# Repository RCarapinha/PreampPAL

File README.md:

# PreampPAL

Project done in 3th year of Masters.

# Description

The goal of this team is to perform a low-noise pre-amplifier that amplifies the needle signal to a line level signal. To accomplish this we started by understanding what was a preamplifier for a record player, namely, what was a preamplifier with reverse RIAA equalization that would amplify the needle signal to a line level signal.

So this team is responsible for the electronics of the turntable audio. This task consists of manipulating low-value and very sensitive voltages. 

# 1st Step: Tests and Simulation

Having said this, we started the search for a preamplifier that corresponded to our needs, i.e. a preamplifier that applied what was described above and low noise (because the values received by the needle are very low).

We chose a range of preamplifiers and set out for the simulation phase using the LTSpice program.

We performed several simulations in LTSpice in terms of noise and equalization in order to choose the best pre-amplifier. At the end of this phase we started to develop the circuit.

# 2nd Step: Breadboard Tests

The first test to be performed was to make sure that the voltage regulator (low noise) correctly converted the value from 5V to 3.3V, and this test was successful. The second test was to verify the amplification and RIAA equalization. For this, a weak signal was applied to the input and we compared the output values obtained with the theoretical output values.

# 3rd Step: PCB Design

After we carried out the tests and validated the operation of the circuit, the next step of the team was to develop the PCB (in EAGLE software) so that we could finish the work.

# 4rd Step: Final Work

Once the PCB has been designed, we start to build the board and assemble the components on it, something that must be done with great care to avoid errors or noise. Finally, we tried to isolate the whole board, for a better functioning.

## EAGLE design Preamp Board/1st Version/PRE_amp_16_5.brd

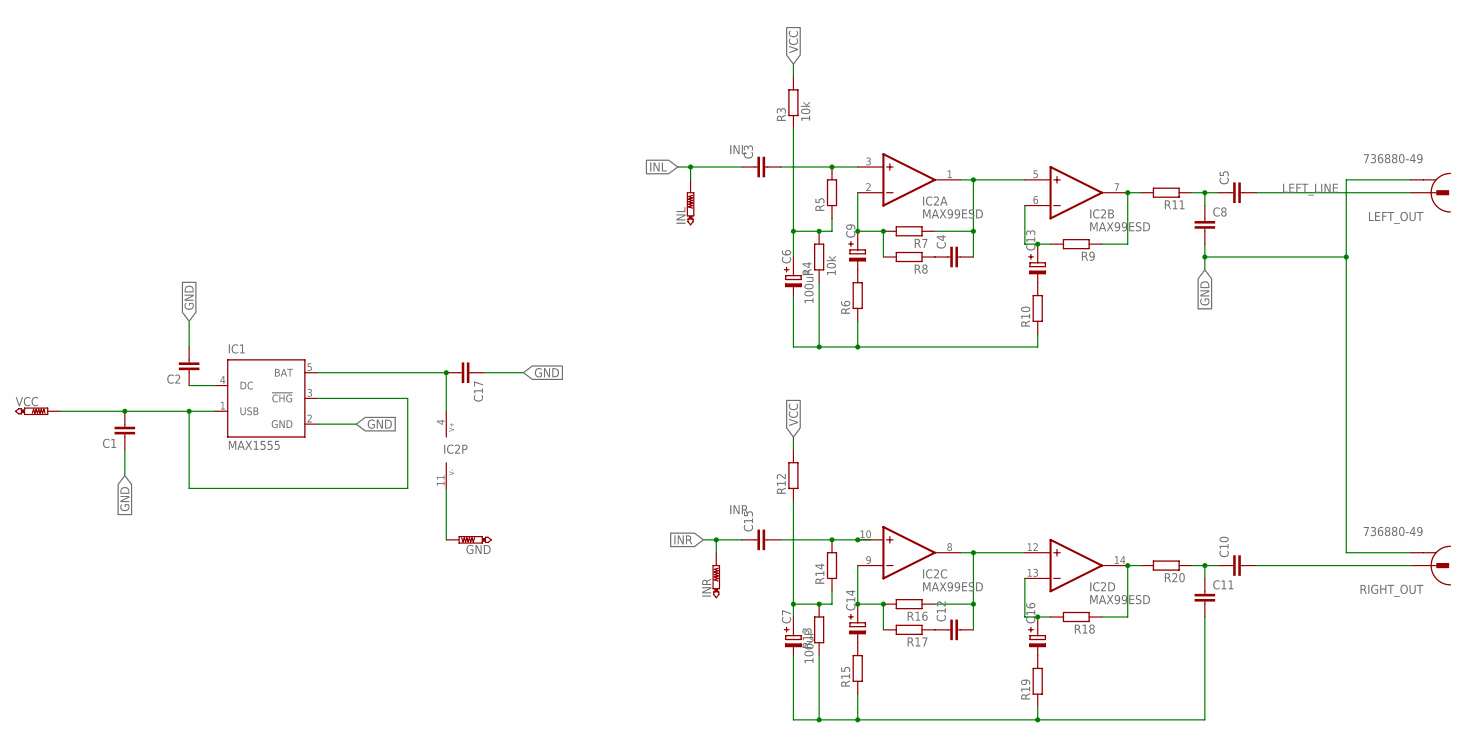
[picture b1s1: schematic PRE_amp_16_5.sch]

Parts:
C1, C2, C3, C4, C5, C8, C10, C11, C12, C15, C17: C-EUC0805; C0805
C6, C7: 100uF; SV-D
C9, C13, C14, C16: C-PR-SMD-SV-B; SV-B
GND: PTR1PAD1-13Y; P1-13Y
IC1: MAX1555; SOT23-5L
IC2: MAX99ESD; SO14
INL: PTR1PAD1-13Y; P1-13Y
INR: PTR1PAD1-13Y; P1-13Y
LEFT_OUT: 736880-49
R3, R4: 10k; R1206
R5, R6, R7, R8, R9, R10, R11, R12, R13, R14, R15, R16, R17, R18, R19, R20: R-EU_R1206; R1206
RIGHT_OUT: 736880-49
VCC: PTR1PAD1-13Y; P1-13Y

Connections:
GND: C1.1, C2.2, C6.-, C7.-, C8.2, C11.2, C17.1, GND.1, IC1.2 (GND), IC2.11 (V-), LEFT_OUT.2, R4.1, R6.1, R10.1, R13.1, R15.1, R19.1, RIGHT_OUT.2
INL: C3.1, INL.1
INR: C15.1, INR.1
LEFT_LINE: C5.2, LEFT_OUT.1
unnamed: C3.2, IC2.3 (+IN), R5.2
unnamed: C6.+, R3.1, R4.2, R5.1
unnamed: C15.2, IC2.10 (+IN), R14.2
unnamed: C7.+, R12.1, R13.2, R14.1
unnamed: IC2.7 (OUT), R9.1, R11.2
unnamed: C9.-, R6.2
unnamed: C4.1, R8.1
unnamed: C12.1, R17.1
unnamed: C9.+, IC2.2 (-IN), R7.2, R8.2
unnamed: C13.-, R10.2
unnamed: C5.1, C8.1, R11.1
unnamed: C14.-, R15.2
unnamed: C13.+, IC2.6 (-IN), R9.2
unnamed: C1.2, IC1.1 (USB), IC1.3 (!CHG), VCC.1
unnamed: C12.2, IC2.8 (OUT), IC2.12 (+IN), R16.1
unnamed: C14.+, IC2.9 (-IN), R16.2, R17.2
unnamed: C16.-, R19.2
unnamed: IC2.14 (OUT), R18.1, R20.2
unnamed: C4.2, IC2.1 (OUT), IC2.5 (+IN), R7.1
unnamed: C16.+, IC2.13 (-IN), R18.2
unnamed: C17.2, IC1.5 (BAT), IC2.4 (V+)
unnamed: C2.1, IC1.4 (DC)
unnamed: C10.2, RIGHT_OUT.1
NS2: C10.1, C11.1, R20.1
VCC: R3.2, R12.2

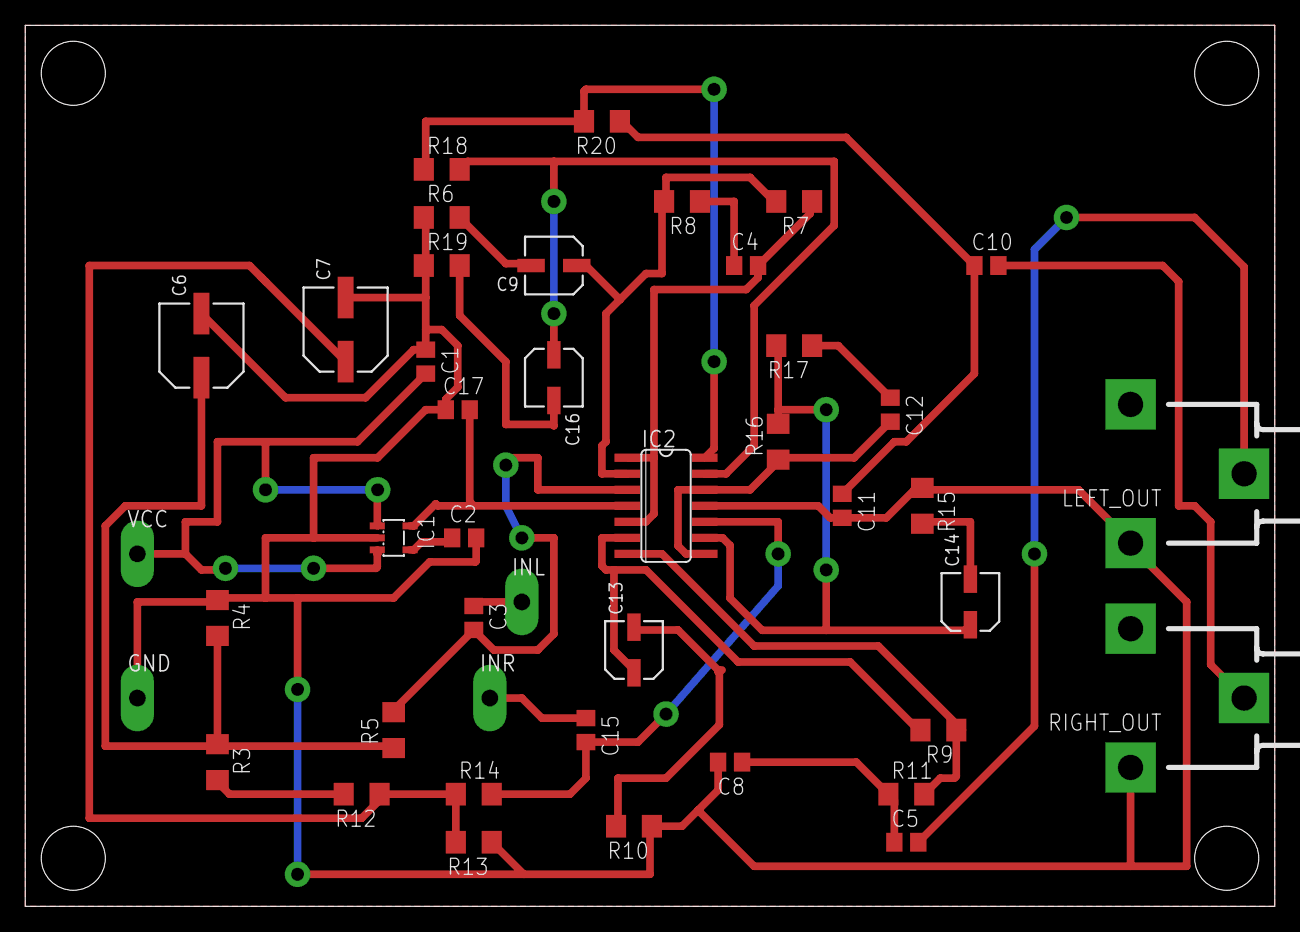
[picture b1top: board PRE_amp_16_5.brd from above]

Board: 2 copper layers, 99.1 x 69.9 mm, 43 parts (0 on the bottom side), 29 nets.

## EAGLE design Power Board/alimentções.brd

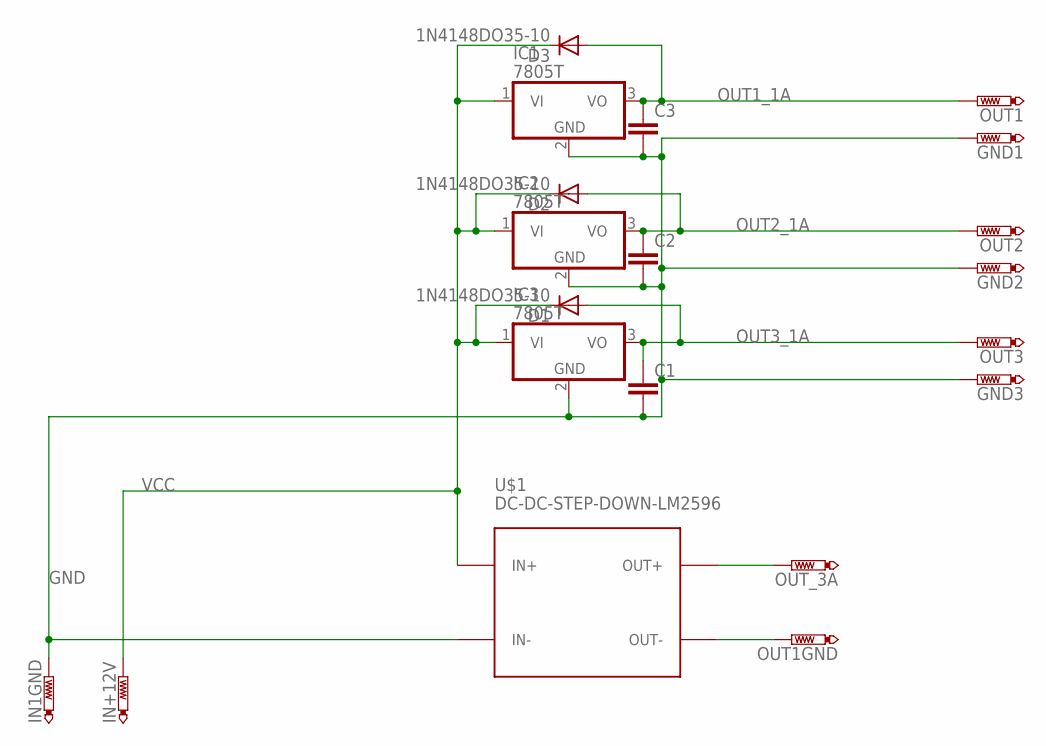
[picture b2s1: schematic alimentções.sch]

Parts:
C1, C2, C3: C-EU050-035X075; C050-035X075
D1, D2, D3: 1N4148DO35-10; DO35-10
GND1, GND2, GND3: PTR1PAD1-13Y; P1-13Y
IC1, IC2, IC3: 7805T; TO220H
IN1GND: PTR1PAD1-13Y; P1-13Y
IN+12V: PTR1PAD1-13Y; P1-13Y
OUT1, OUT1GND, OUT2, OUT3: PTR1PAD1-13Y; P1-13Y
OUT_3A: PTR1PAD1-13Y; P1-13Y
U$1: DC-DC-STEP-DOWN-LM2596

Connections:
GND: C1.2, C2.2, C3.2, GND1.TP, GND2.TP, GND3.TP, IC1.2 (GND), IC2.2 (GND), IC3.2 (GND), IN1GND.TP, U$1.IN-
unnamed: OUT1GND.TP, U$1.OUT-
unnamed: OUT_3A.TP, U$1.OUT+
OUT1_1A: C3.1, D3.A, IC1.3 (VO), OUT1.TP
OUT2_1A: C2.1, D2.A, IC2.3 (VO), OUT2.TP
OUT3_1A: C1.1, D1.A, IC3.3 (VO), OUT3.TP
VCC: D1.C, D2.C, D3.C, IC1.1 (VI), IC2.1 (VI), IC3.1 (VI), IN+12V.TP, U$1.IN+

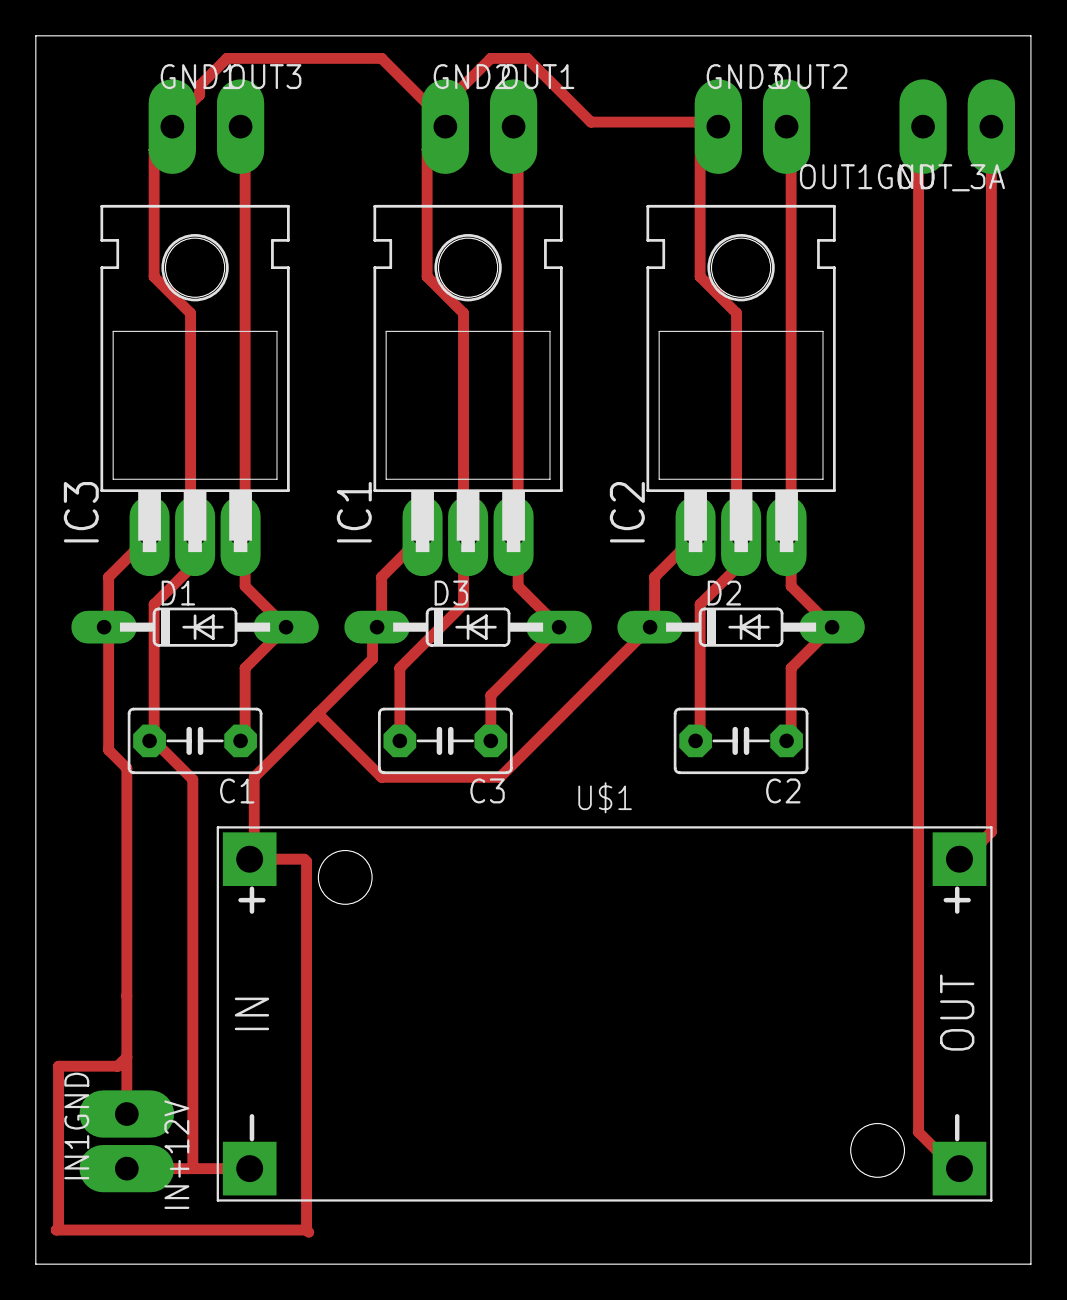
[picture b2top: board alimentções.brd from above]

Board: 2 copper layers, 55.5 x 68.6 mm, 20 parts (0 on the bottom side), 7 nets.

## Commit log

2020-08-02 images

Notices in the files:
parts and their libraries:
diy-modules: Released under the Creative Commons Attribution 4.0 International License: http://creativecommons.org/licenses/by/4.0
cap-pan40: Copyright (C) 2004, Bob Starr
